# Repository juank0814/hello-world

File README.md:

# hello-world....
justificación de repositorio
cambios realizados

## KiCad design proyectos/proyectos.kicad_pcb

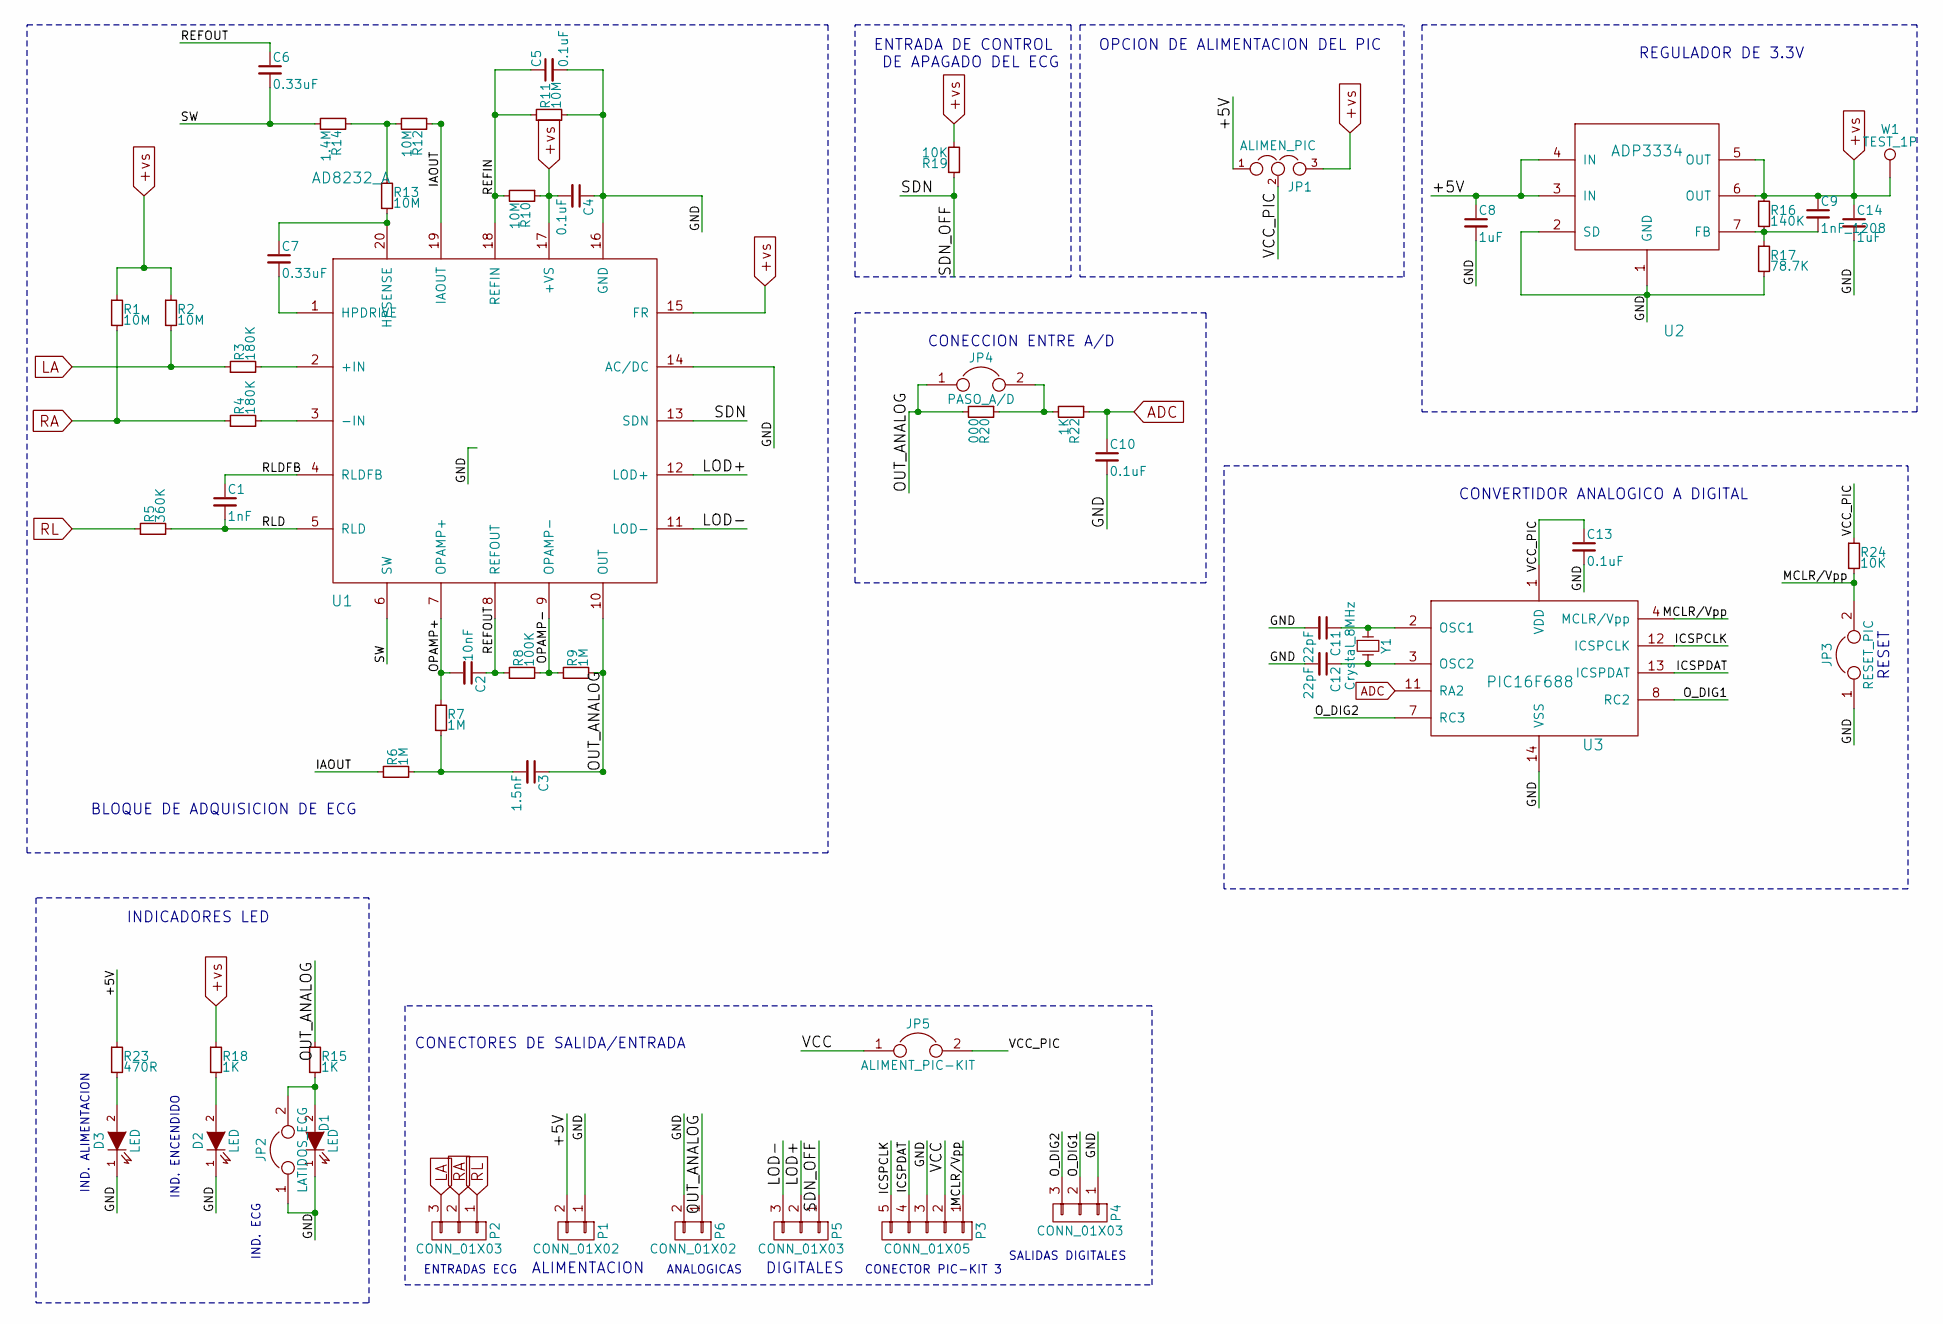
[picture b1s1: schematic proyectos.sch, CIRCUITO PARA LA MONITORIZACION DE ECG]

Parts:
C1: 1nF; C_0805_HandSoldering
C2: 10nF; C_0805_HandSoldering
C3: 1.5nF; C_0805_HandSoldering
C4, C5, C10, C13: 0.1uF; C_0805_HandSoldering
C6, C7: 0.33uF; C_0805_HandSoldering
C8, C14: 1uF; C_0805_HandSoldering
C9: 1nF_1208; C_1206_HandSoldering
C11, C12: 22pF; C_0805_HandSoldering
D1, D2, D3: LED; LED_0805
JP1: ALIMEN_PIC; Pin_Header_Straight_1x03_Pitch2.54mm
JP2: LATIDOS_ECG; Pin_Header_Straight_1x02_Pitch2.54mm
JP3: RESET_PIC; Pin_Header_Straight_1x02_Pitch2.54mm
JP4: PASO_A/D; Pin_Header_Straight_1x02_Pitch2.54mm
JP5: ALIMENT_PIC-KIT; Pin_Header_Straight_1x02_Pitch2.54mm
P1, P6: CONN_01X02; Pin_Header_Straight_1x02_Pitch2.54mm
P2, P4, P5: CONN_01X03; Pin_Header_Straight_1x03_Pitch2.54mm
P3: CONN_01X05; Pin_Header_Angled_1x05_Pitch2.54mm
R1, R2, R10, R11, R12, R13: 10M; R_0805_HandSoldering
R3, R4: 180K; R_0805_HandSoldering
R5: 360K; R_0805_HandSoldering
R6, R7, R9: 1M; R_0805_HandSoldering
R8: 100K; R_0805_HandSoldering
R14: 1.4M; R_0805_HandSoldering
R15, R18, R22: 1K; R_0805_HandSoldering
R16: 140K; R_0805_HandSoldering
R17: 78.7K; R_0805_HandSoldering
R19, R24: 10K; R_0805_HandSoldering
R20: 000; R_0805_HandSoldering
R23: 470R; R_0805_HandSoldering
U1: AD8232_A; AD8232_ECG
U2: ADP3334; SOIC-8_3.9x4.9mm_Pitch1.27mm
U3: PIC16F688; SOIC-14_3.9x8.7mm_Pitch1.27mm
W1: TEST_1P; Measurement_Point_Round-TH_Small
Y1: Crystal_8MHz; Crystal_SMD_Abracon_ABM3-2pin_5.0x3.2mm_HandSoldering

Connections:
+vs: C4.2, C9.1, C14.1, JP1.3, R1.1, R2.1, R10.1, R16.1, R18.1, R19.2, U1.15 (FR), U1.17 (+VS), U2.5 (OUT), U2.6 (OUT), W1.1
/+5V: C8.1, JP1.1, P1.2, R23.1, U2.3 (IN), U2.4 (IN)
/GND: C4.1, C5.2, C8.2, C10.2, C11.2, C12.2, C13.2, C14.2, D1.1 (K), D2.1 (K), D3.1 (K), JP2.1, JP3.1, P1.1, P3.3, P4.1, P6.2, R11.2, R17.2, U1.14 (AC/DC), U1.16 (GND), U1.21 (GND), U2.1 (GND), U2.2 (SD), U3.14 (VSS)
/IAOUT: R6.1, R12.1, U1.19 (IAOUT)
/ICSPCLK: P3.5, U3.12 (ICSPCLK)
/ICSPDAT: P3.4, U3.13 (ICSPDAT)
/LOD+: P5.2 (LA), U1.12 (LOD+)
/LOD-: P5.3 (RA), U1.11 (LOD-)
/MCLR/Vpp: JP3.2, P3.1, R24.2, U3.4 (MCLR/Vpp)
/OPAMP+: C2.2, R7.1, U1.7 (OPAMP+)
/OUT_ANALOG: C3.1, JP4.1, P6.1, R9.2, R15.1, R20.2, U1.10 (OUT)
/O_DIG1: P4.2, U3.8 (RC2)
/O_DIG2: P4.3, U3.7 (RC3)
/REFIN: C5.1, R10.2, R11.1, U1.18 (REFIN)
/REFOUT: C2.1, C6.1, R8.1, U1.8 (REFOUT)
/RLD: C1.2, R5.2, U1.5 (RLD)
/RLDFB: C1.1, U1.4 (RLDFB)
/SDN: P5.1 (RL), R19.1, U1.13 (SDN)
/SW: C6.2, R14.2, U1.6 (SW)
/VCC: JP5.1, P3.2
/VCC_PIC: C13.1, JP1.2, JP5.2, R24.1, U3.1 (VDD)
ADC: C10.1, R22.1, U3.11 (RA2)
LA: P2.3 (RA), R2.2, R3.1
unnamed: C3.2, R6.2, R7.2
unnamed: C7.1, R13.2, U1.20 (HPSENSE)
unnamed: C7.2, U1.1 (HPDRIVE)
unnamed: C9.2, R16.2, R17.1, U2.7 (FB)
unnamed: C11.1, U3.2 (OSC1), Y1.1
unnamed: C12.1, U3.3 (OSC2), Y1.2
unnamed: D1.2 (A), JP2.2, R15.2
unnamed: D2.2 (A), R18.2
unnamed: D3.2 (A), R23.2
unnamed: JP4.2, R20.1, R22.2
unnamed: R3.2, U1.2 (+IN)
unnamed: R4.2, U1.3 (-IN)
unnamed: R8.2, R9.1, U1.9 (OPAMP-)
unnamed: R12.2, R13.1, R14.1
RA: P2.2 (LA), R1.2, R4.1
RL: P2.1 (RL), R5.1

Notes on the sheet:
REGULADOR DE 3.3V
INDICADORES LED
IND. ENCENDIDO
IND. ECG
CONECTORES DE SALIDA/ENTRADA
ENTRADAS ECG
IND. ALIMENTACION
CONECTOR PIC-KIT 3
SALIDAS DIGITALES
ANALOGICAS
CONECCION ENTRE A/D
BLOQUE DE ADQUISICION DE ECG
CONVERTIDOR ANALOGICO A DIGITAL
RESET
OPCION DE ALIMENTACION DEL PIC
ENTRADA DE CONTROL DE APAGADO DEL ECG
DIGITALES
ALIMENTACION

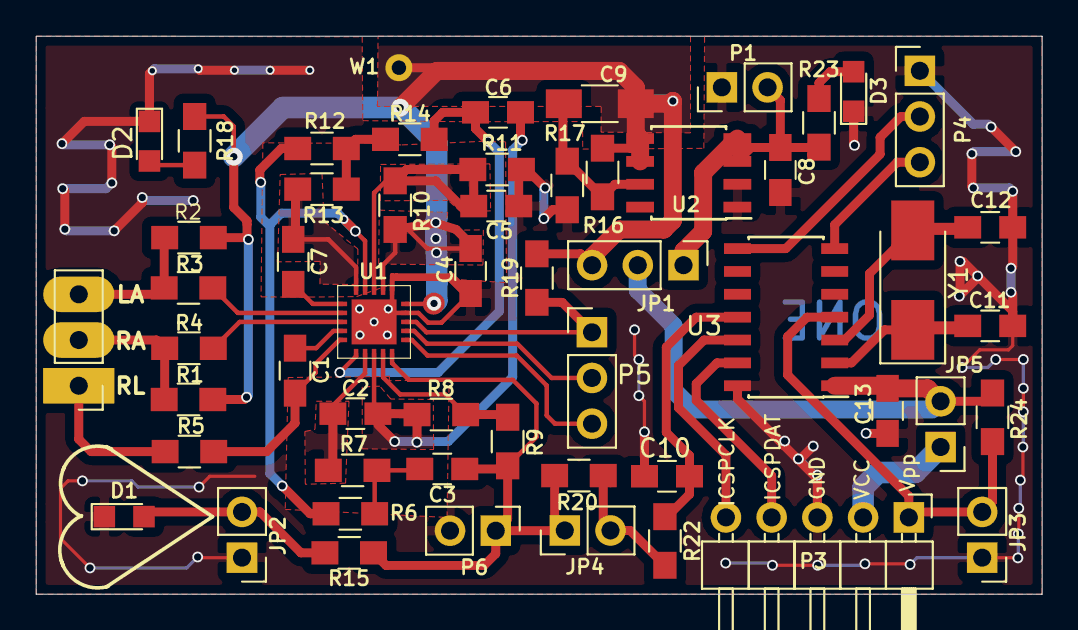
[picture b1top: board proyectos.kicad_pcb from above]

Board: 2 copper layers, 55.9 x 31.0 mm, 56 parts (1 on the bottom side), 39 nets.

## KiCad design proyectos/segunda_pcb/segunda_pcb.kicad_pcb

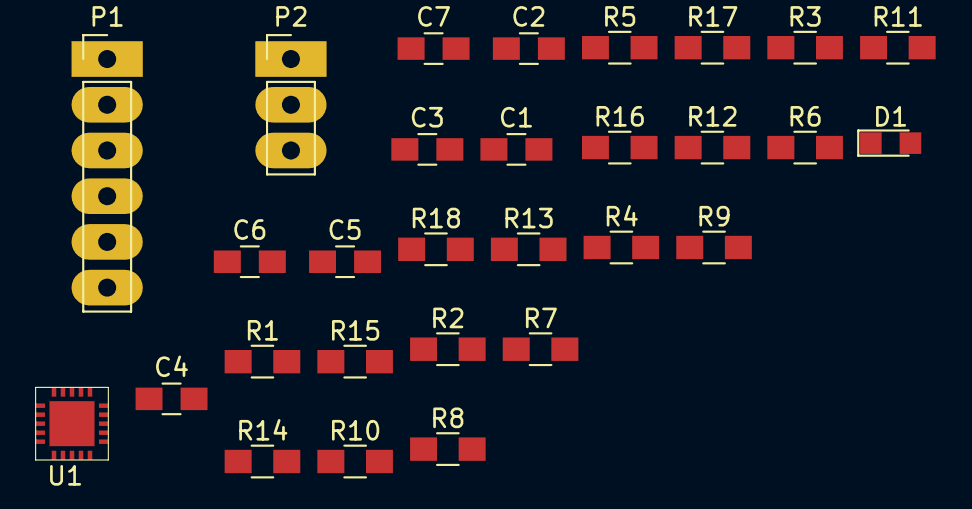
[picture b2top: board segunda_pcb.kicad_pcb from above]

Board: 2 copper layers, 29 parts (0 on the bottom side), 26 nets, no tracks yet.

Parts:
C1: 1nF; C_0805_HandSoldering
C2: 10nF; C_0805_HandSoldering
C3: 1,5nF; C_0805_HandSoldering
C4, C5: 0,1uF; C_0805_HandSoldering
C6, C7: 0,33uF; C_0805_HandSoldering
D1: LED; LED_0805
P1: CONN_01X06; Pin_Header_Straight_1x06_Pitch2.54mm
P2: CONN_01X03; Pin_Header_Straight_1x03_Pitch2.54mm
R1, R2, R10, R11, R12, R13: 10M; R_0805_HandSoldering
R3, R4: 180K; R_0805_HandSoldering
R5: 360K; R_0805_HandSoldering
R6, R7, R9: 1M; R_0805_HandSoldering
R8: 100K; R_0805_HandSoldering
R14: 1,4M; R_0805_HandSoldering
R15: 1K; R_0805_HandSoldering
R16, R17: 000; R_0805_HandSoldering
R18: DNP; R_0805_HandSoldering
U1: AD8232; AD8232_ECG

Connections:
/IAOUT: R6.1, R12.2, U1.19
/LOD+: P1.2, U1.12
/LOD-: P1.3, U1.11
/OPAMP+: C2.1, R7.1, U1.7
/OPAMP-: R8.2, R9.1, U1.9
/OUT: C3.2, P1.4, R9.2, R15.1, U1.10
/REFOUT: C2.2, C6.1, R8.1, U1.8
/SDN: P1.1, U1.13
/SW: C6.2, R14.1, U1.6
GND: C4.2, C5.2, D1.1, P1.6, R11.2, R17.1, U1.16, U1.21
unnamed: C1.1, U1.4
unnamed: C1.2, R5.2, U1.5
unnamed: C3.1, R6.2, R7.2
unnamed: C5.1, R10.1, R11.1, U1.18
unnamed: C7.1, U1.1
unnamed: C7.2, R13.2, U1.20
unnamed: D1.2, R15.2
unnamed: P2.1, R5.1
unnamed: P2.2, R1.2, R4.1
unnamed: P2.3, R2.2, R3.1
unnamed: R1.1, R2.1, R16.2
unnamed: R3.2, U1.2
unnamed: R4.2, U1.3
unnamed: R12.1, R13.1, R14.2
unnamed: R17.2, R18.2, U1.14
VCC: C4.1, P1.5, R10.2, R16.1, R18.1, U1.15, U1.17

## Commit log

2017-04-25 version ecg 1.1
    reacomodacion de pines de entrada
2017-05-02 project_V.1.1
    anexo actividades del modulo de minimo sangrado
2017-05-04 version ECG 1.2
    REGULADOR
2017-05-10 version ECG 1.3
    MODIFICACION DE ESQUEMATICO
2017-05-16 version ECG 1.4
    INCORPORACION DE PIC Y REGULADOR
2017-05-16 version ECG 1.5
    MODIFICACION DE PAD TORNILLOS
2017-05-16 VERSION 1.6 ECG
    SIN PANELIZADO Y CON BASE
2017-05-16 VERSION 1.7 ECG Y PIC
    NUEVA VERSION
2017-05-18 VERSION 1.8 ECG Y PIC
    CAMBIO DE REGULADOR POR ADP3334
2017-05-18 version 1.9 ECG Y PIC
    nuevo cambio de regulador y logo
2017-05-22 version 2.0 ecg y pic
    archivo para panelizar
